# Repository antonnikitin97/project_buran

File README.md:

# project_buran
Files pertaining to my home-made Stream Deck project. 

## Motivation
I don't want to pay £150 for a stream deck

## Why Buran?
I decided some time ago to name all my personal projects after Russian space missions, буран (meaning, blizzard in Russian) was the Soviet Union's/Russia's attempt at a fully automated shuttle, it flew once successfully but was canned due to funding issues and the only existing model being destroyed.

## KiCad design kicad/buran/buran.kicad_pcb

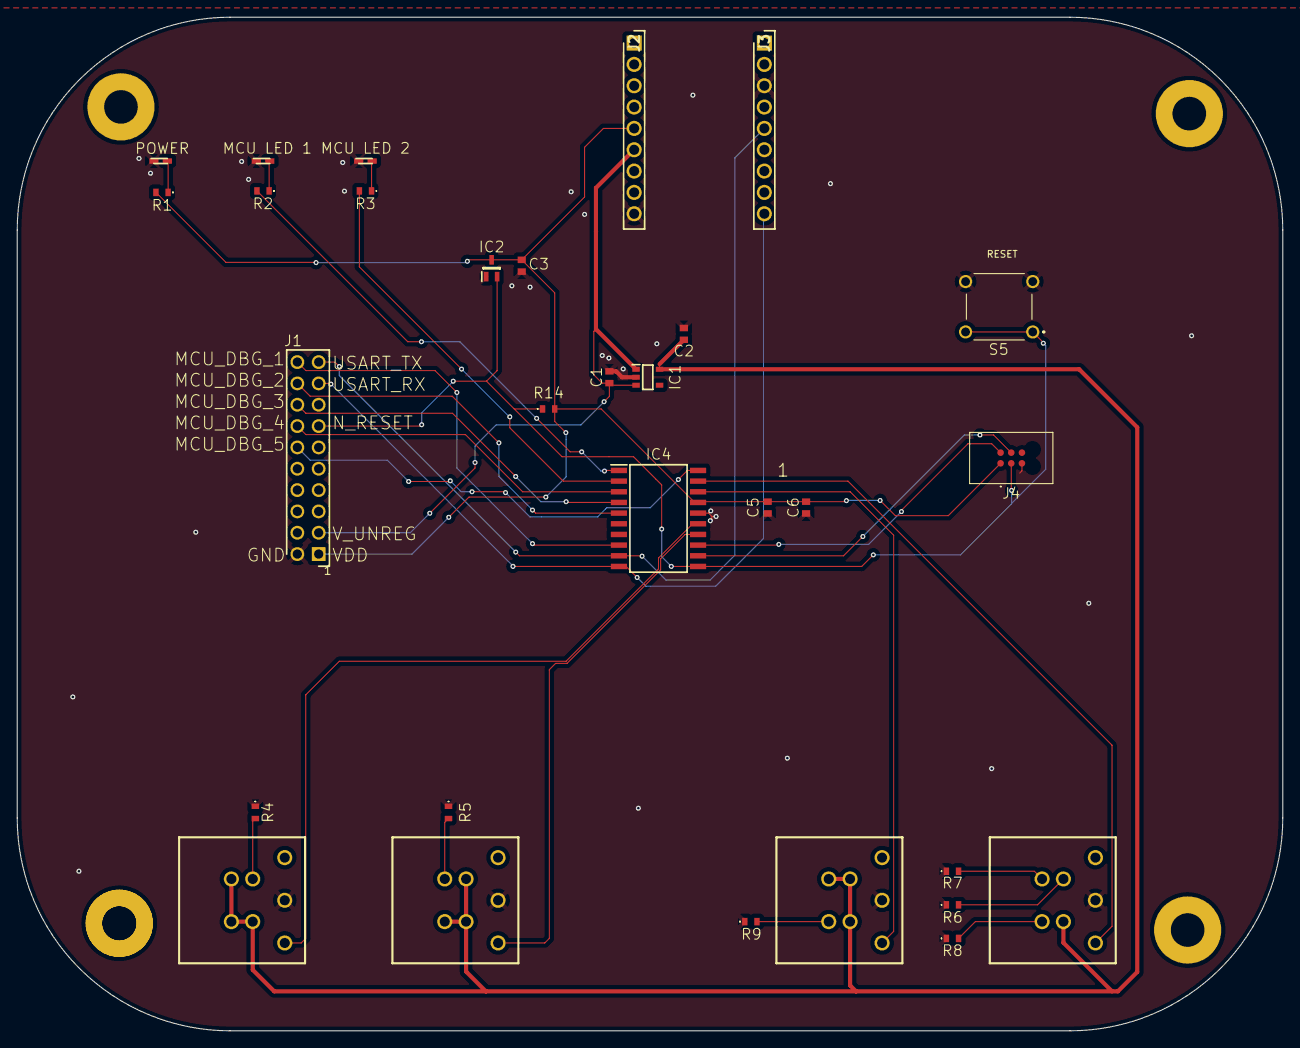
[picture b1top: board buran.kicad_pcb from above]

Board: 2 copper layers, 150.7 x 120.7 mm, 30 parts (0 on the bottom side), 29 nets.

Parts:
C1, C2: 1uF; CAPC1608X87N
C3, C5: 100nF; CAPC1608X87N
C6: 4.7uF; CAPC1608X87N
IC1: XC6210B332MR; SOT95P280X130-5N
IC2: MAX803SQ308D2T1G; SOT65P220X100-3N
IC4: ATSAMD11D14A-SSNT; SOIC127P1032X265-20N
J1: M20-9761042; HDRV20W64P254_2X10_2540X508X838P
J2, J3: M20-7820946; RHDR9W70P0X254_1X9_2326X250X865P
J4: TC2030-CTX-NL; TC2030MCPNL10
MCU LED 1, MCU LED 2: HSMA-C120; LEDM166X110N
POWER : HSMA-C120; LEDM166X110N
R1, R2, R3, R4, R5, R6, R7, R8, R9: 30R; ERA3AEB101V
R14: 4K7; ERA3AEB101V
S1, S2, S3, S4: PB26-13M RGB LED
S5: ESE20C321

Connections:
/MCU_DBG_1: IC4.8 (PA16), J1.20
/MCU_DBG_2: IC4.5 (PA09), J1.18
/MCU_DBG_3: IC4.4 (PA08), J1.16
/MCU_DBG_4: IC4.3 (PA07), J1.14
/MCU_DBG_5: IC4.20 (PA04), J1.12
/MCU_LED_1: IC4.1 (PA05), R2.2
/MCU_LED_2: IC4.2 (PA06), R3.2
/MCU_S1: IC4.15 (PA25), S1.1 (COM)
/MCU_S2: IC4.14 (PA24), S2.1 (COM)
/MCU_S3: IC4.18 (PA02), S3.1 (COM)
/MCU_S4: IC4.19 (PA03), S4.1 (COM)
/N_RESET: IC2.2 (~RESET), IC4.11 (PA28/~RST), J1.13, J4.3, R14.1, S5.A1, S5.C1
/SWCLK: IC4.12 (PA30), J4.4
/SWDIO: IC4.13 (PA31), J4.2
/USART_RX: IC4.10 (PA23), J1.17, J3.9
/USART_TX: IC4.9 (PA22), J1.19, J3.5
/V_LEDs: C2.2, IC1.5 (VOUT), S1.4 (L2), S1.6 (L4), S1.7 (L3), S2.4 (L2), S2.5 (L1), S2.7 (L3), S3.4 (L2), S3.5 (L1), S3.6 (L4), S4.4 (L2)
/V_UNREG: C1.2, IC1.1 (VIN), IC1.3 (CE), J1.3, J2.6
GND: C1.1, C2.1, C3.1, C5.1, C6.1, IC1.2 (VSS), IC2.1 (GND), IC4.16 (GND), J1.2, J2.9, J3.3, J4.5, MCU LED 1.1, MCU LED 2.1, POWER.1, R4.1, R5.1, R6.1, R7.1, R8.1, R9.1, S1.2 (NO), S2.2 (NO), S3.2 (NO), S4.2 (NO), S5.B1, S5.D1
unnamed: MCU LED 1.2, R2.1
unnamed: MCU LED 2.2, R3.1
unnamed: POWER.2, R1.1
unnamed: R4.2, S1.5 (L1)
unnamed: R5.2, S2.6 (L4)
unnamed: R9.2, S3.7 (L3)
unnamed: R6.2, S4.5 (L1)
unnamed: R8.2, S4.7 (L3)
unnamed: R7.2, S4.6 (L4)
VDD: C3.2, C5.2, C6.2, IC2.3 (VCC), IC4.17 (VDDIO/IN/ANA), J1.1, J2.5, J4.1, R1.2, R14.2

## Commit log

2020-12-24 initial project upload
2020-12-26 modify PCB shape to 150x80mm
2020-12-27 add switches, usb components, LEDs, MCU
2020-12-28 add labels for connections
2020-12-28 add power regulation block and decoupling caps
2020-12-28 add further labels to ports on components
2020-12-28 add usb series resistors
2020-12-28 add components to layout
2020-12-29 update page size to a2 to give more space
2020-12-29 add labels to mcu, switch connections
2020-12-29 add updi header to schematic
2020-12-29 add crystal oscilator for usb
2020-12-30 update schematic with usb ic net labels
2021-01-17 update project
2021-01-27 update schematic for component models
2021-02-10 update pcb and schematic
2021-02-10 update components on pcb, initial layout
2021-02-12 update pcb layout for 4 switches
2021-03-14 revamp schematic, remove usb controller, change microcontroller
2021-03-14 change PCB shape, add new components
2021-03-15 add power-on-reset circuitry
2021-03-16 preliminary placement of components on pcb
2021-03-16 add decoupling cap to mcu vcc line
2021-03-16 whole project commit
2021-03-17 update power lines for regulator
2021-03-17 add new RGB driver part (different footprint)
2021-03-19 add indicator LED to schematic, change crystal for DRC
2021-03-19 add more indicator leds to schematic
2021-03-20 add output job file for pcb project
2021-03-20 initial software project upload
2021-03-20 change folder structure for pcb files
2021-03-20 Delete Project_Buran directory
    remove old project directory
2021-03-21 preliminary layout
2021-03-21 add decoupling cap for rgb driver vcc
2021-03-21 add in decoup cap after issue with schem
2021-03-21 finish prelim layout, add gnd vias and stitching
2021-03-21 add more vias for grounding
2021-03-22 add some more vias for good grounding
2021-03-22 add libraries to version control
2021-03-23 move sda line away from 32khz crystal, change length of usb pairs
2021-03-27 update schematic component values for resistors and capacitors
2021-03-27 add reference files for v1.0 to project
2021-03-28 add new software
2021-04-15 remove project buran controller from repo
2021-04-15 add gitignore to repo
2021-04-15 update revision to a02
2021-04-15 readd a01 and rename to general project_buran
2021-04-15 add new connector to pcb layout
2021-04-15 add new usb connector to schematic
2021-04-15 update revision number
2021-04-17 add thermal relief to pads to smd pads that connect to GND plane
2021-04-17 update meme format, move some layout for better GND connection
2021-04-17 add label to programming header for convenience
2021-04-17 change led labels to correct names
2021-04-17 final v1.1 layout
2021-04-18 move vias away from doge
2021-04-18 fix altium project after removal of other files
2021-05-16 add new component library for new rgb buttons
2021-05-16 update schematic for v2. Add more buttons, change some MCU connections
2021-05-17 begin layout for v2
2021-05-21 work on v2 layout
2021-05-22 v1.2 - add 1.27mm programming header
2021-05-22 add v1.2 reference files
2021-05-22 add reference files for v1.2
2021-05-22 remove uneeded schematic files
2021-07-10 add io exapander and test points for v2
2021-12-04 replace usb header with pins
2021-12-04 replace usb with serial header
2021-12-04 replace usb header with serial header
2022-07-19 Update files
2022-09-25 add i2c usb chip
2022-11-13 Update schematic, begin new layout
2024-01-21 Add kicad files
2024-05-22 kicad files
2024-05-31 update kicad
2024-06-09 add reference files for 3.1 (new usb header)
2024-06-09 add v3.0 reference files
2024-08-10 modify buran hardware
2024-08-10 datasheets
2025-02-26 reference files for v3.0
